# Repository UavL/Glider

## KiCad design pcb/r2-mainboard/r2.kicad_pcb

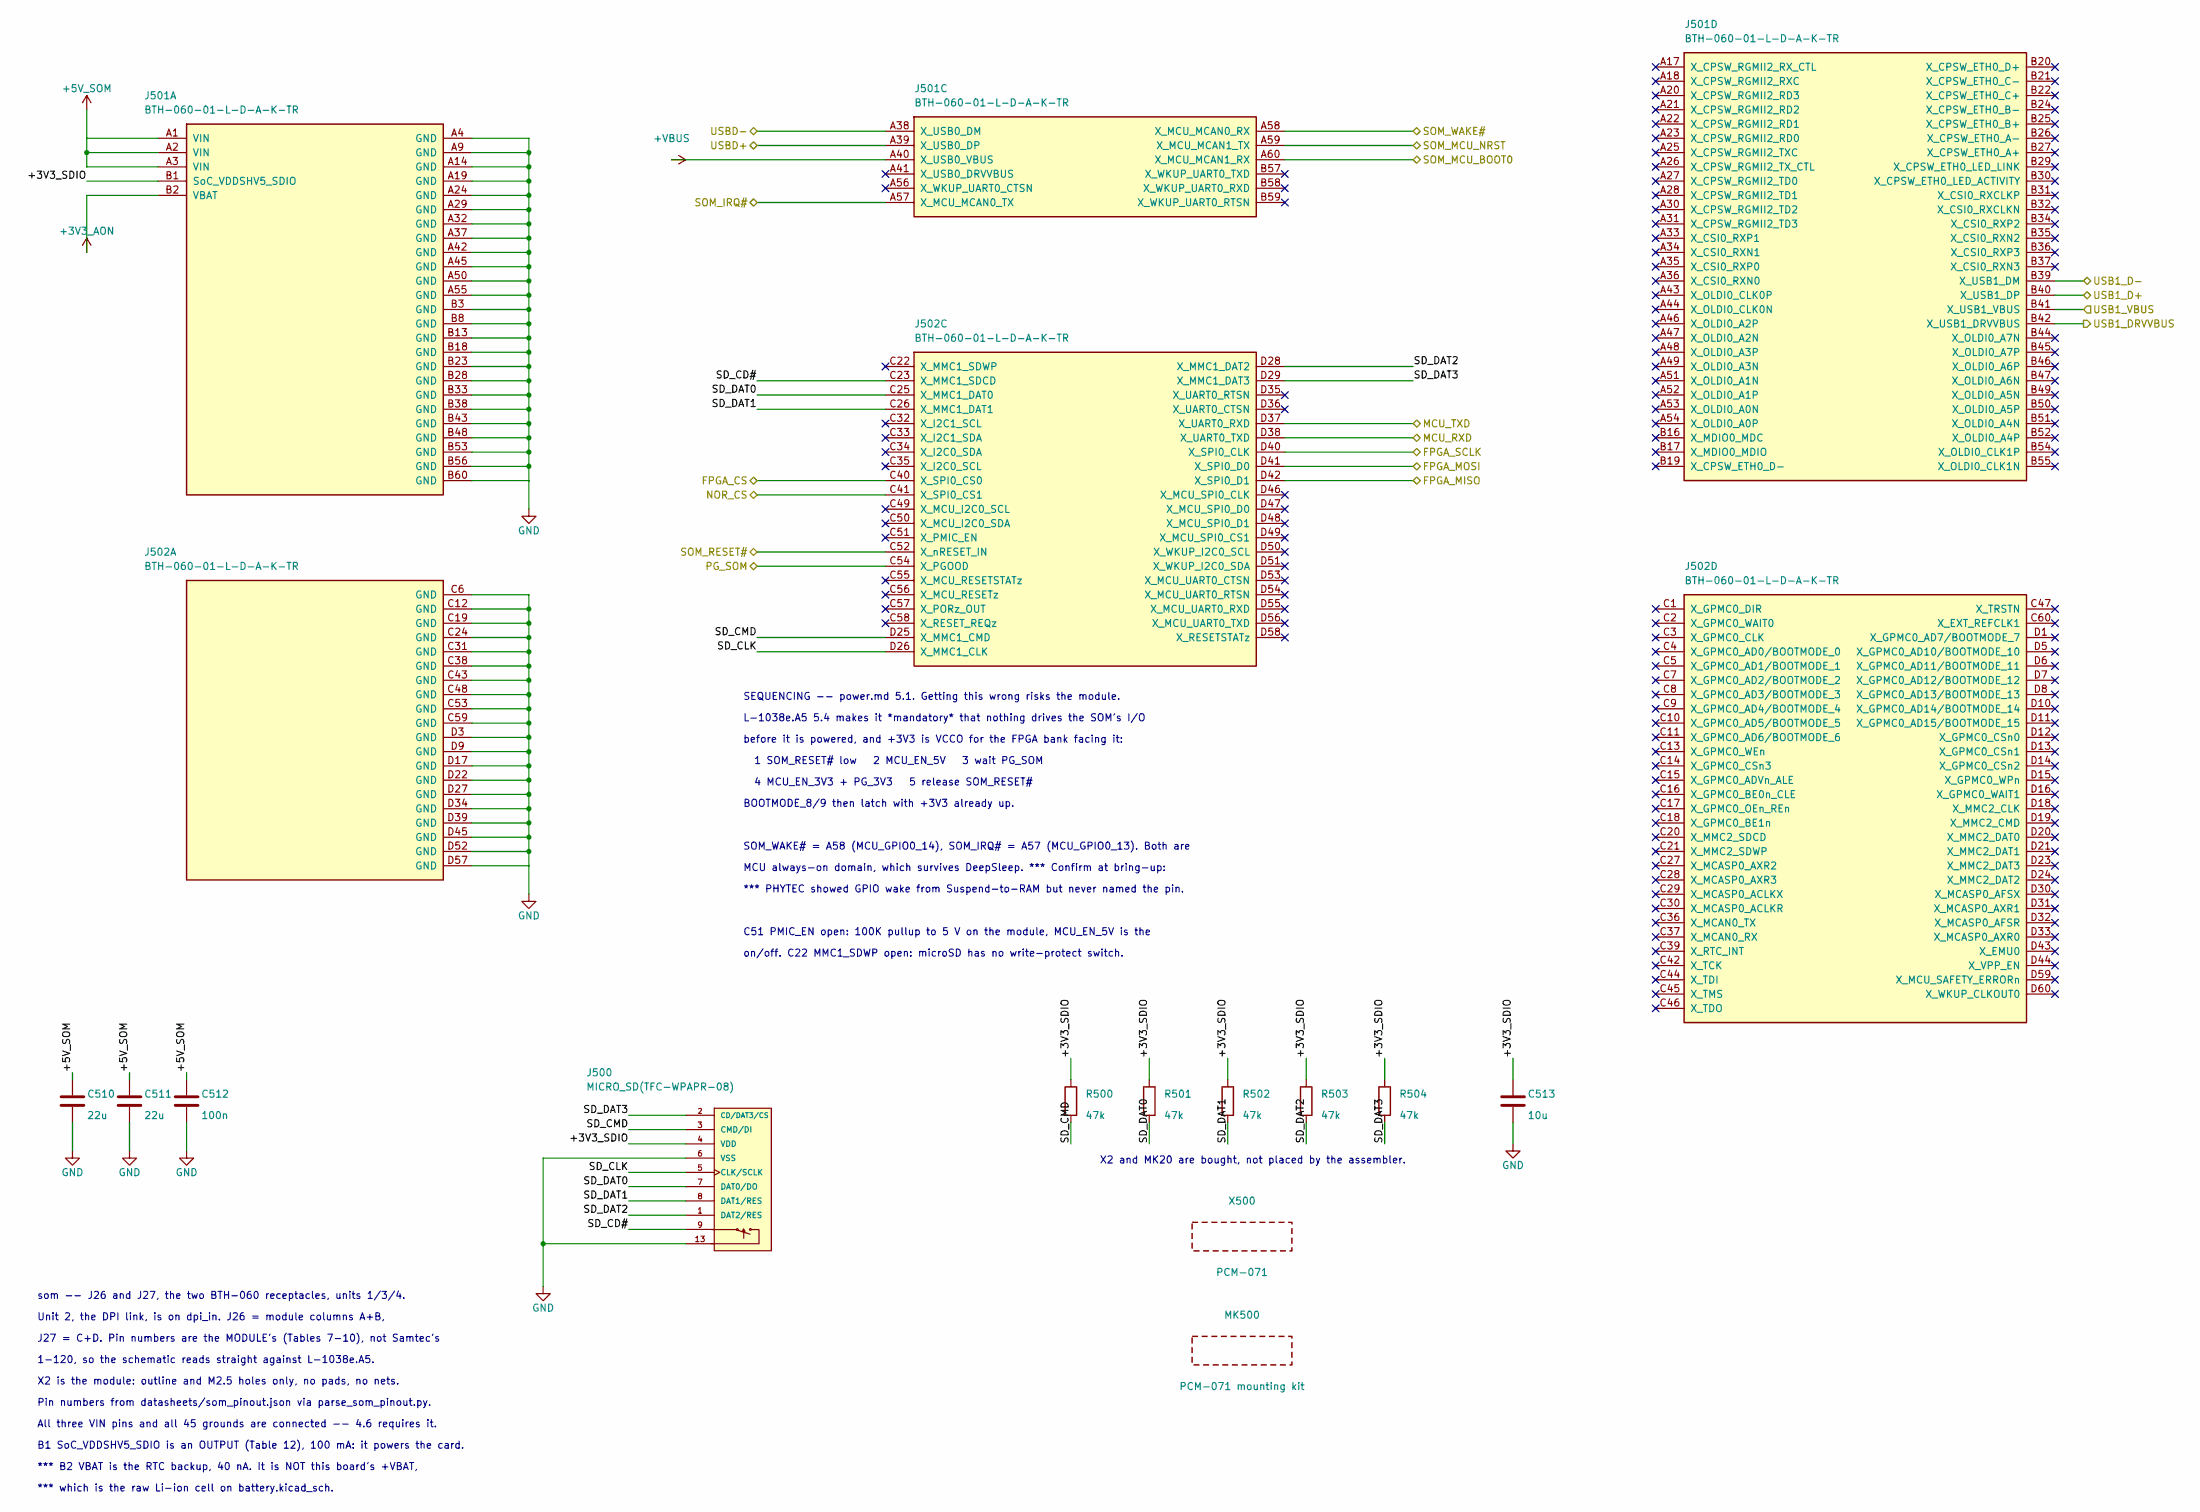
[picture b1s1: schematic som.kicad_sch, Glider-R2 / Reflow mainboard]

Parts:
C510, C511: 22u; C_0805_2012Metric
C512: 100n; C_0402_1005Metric
C513: 10u; C_0805_2012Metric
J500: MICRO_SD(TFC-WPAPR-08); TFC-WPAPR-08
J501: BTH-060-01-L-D-A-K-TR; BTH-060-01-L-D-A-K_AB; MPN BTH-060-01-L-D-A-K-TR; LCSC C3646540
J502: BTH-060-01-L-D-A-K-TR; BTH-060-01-L-D-A-K_CD; MPN BTH-060-01-L-D-A-K-TR; LCSC C3646540
MK500: PCM-071 mounting kit; MPN 2x M2.5x5 F-F standoff, 4x M2.5x4 screw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
R500, R501, R502, R503, R504: 47k; R_0402_1005Metric
X500: PCM-071; PCM-071_Module; MPN PCM-071

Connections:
+3V3_AON: J501.B2 (VBAT); also elsewhere on the board
+5V_SOM: C510.1, C511.1, C512.1, J501.A1 (VIN), J501.A2 (VIN), J501.A3 (VIN); also elsewhere on the board
+VBUS: J501.A40 (X_USB0_VBUS); also elsewhere on the board
/FPGA_CS: J502.C40 (X_SPI0_CS0); also elsewhere on the board
/FPGA_MISO: J502.D42 (X_SPI0_D1); also elsewhere on the board
/FPGA_MOSI: J502.D41 (X_SPI0_D0); also elsewhere on the board
/FPGA_SCLK: J502.D40 (X_SPI0_CLK); also elsewhere on the board
/MCU_RXD: J502.D38 (X_UART0_TXD); also elsewhere on the board
/MCU_TXD: J502.D37 (X_UART0_RXD); also elsewhere on the board
/NOR_CS: J502.C41 (X_SPI0_CS1); also elsewhere on the board
/PG_SOM: J502.C54 (X_PGOOD); also elsewhere on the board
/SOM_IRQ#: J501.A57 (X_MCU_MCAN0_TX); also elsewhere on the board
/SOM_MCU_BOOT0: J501.A60 (X_MCU_MCAN1_RX); also elsewhere on the board
/SOM_MCU_NRST: J501.A59 (X_MCU_MCAN1_TX); also elsewhere on the board
/SOM_RESET#: J502.C52 (X_nRESET_IN); also elsewhere on the board
/SOM_WAKE#: J501.A58 (X_MCU_MCAN0_RX); also elsewhere on the board
/USB1_D+: J501.B40 (X_USB1_DP); also elsewhere on the board
/USB1_D-: J501.B39 (X_USB1_DM); also elsewhere on the board
/USB1_DRVVBUS: J501.B42 (X_USB1_DRVVBUS); also elsewhere on the board
/USB1_VBUS: J501.B41 (X_USB1_VBUS); also elsewhere on the board
/USBD+: J501.A39 (X_USB0_DP); also elsewhere on the board
/USBD-: J501.A38 (X_USB0_DM); also elsewhere on the board
/som/+3V3_SDIO: C513.1, J500.4 (VDD), J501.B1 (SoC_VDDSHV5_SDIO), R500.1, R501.1, R502.1, R503.1, R504.1
/som/SD_CD#: J500.9, J502.C23 (X_MMC1_SDCD)
/som/SD_CLK: J500.5 (CLK/SCLK), J502.D26 (X_MMC1_CLK)
/som/SD_CMD: J500.3 (CMD/DI), J502.D25 (X_MMC1_CMD), R500.2
/som/SD_DAT0: J500.7 (DAT0/DO), J502.C25 (X_MMC1_DAT0), R501.2
/som/SD_DAT1: J500.8 (DAT1/RES), J502.C26 (X_MMC1_DAT1), R502.2
/som/SD_DAT2: J500.1 (DAT2/RES), J502.D28 (X_MMC1_DAT2), R503.2
/som/SD_DAT3: J500.2 (CD/DAT3/CS), J502.D29 (X_MMC1_DAT3), R504.2
GND: C510.2, C511.2, C512.2, C513.2, J500.6 (VSS), J500.10, J500.11, J500.12, J500.13, J501.A4 (GND), J501.A9 (GND), J501.A14 (GND), J501.A19 (GND), J501.A24 (GND), J501.A29 (GND), J501.A32 (GND), J501.A37 (GND), J501.A42 (GND), J501.A45 (GND), J501.A50 (GND), J501.A55 (GND), J501.B3 (GND), J501.B8 (GND), J501.B13 (GND), J501.B18 (GND), J501.B23 (GND), J501.B28 (GND), J501.B33 (GND), J501.B38 (GND), J501.B43 (GND), J501.B48 (GND), J501.B53 (GND), J501.B56 (GND), J501.B60 (GND), J502.C6 (GND), J502.C12 (GND), J502.C19 (GND), J502.C24 (GND), J502.C31 (GND), J502.C38 (GND), J502.C43 (GND), J502.C48 (GND), J502.C53 (GND), J502.C59 (GND), J502.D3 (GND), J502.D9 (GND), J502.D17 (GND), J502.D22 (GND), J502.D27 (GND), J502.D34 (GND), J502.D39 (GND), J502.D45 (GND), J502.D52 (GND), J502.D57 (GND); also elsewhere on the board

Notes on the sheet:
4 MCU_EN_3V3 + PG_3V3 5 release SOM_RESET#
*** B2 VBAT is the RTC backup, 40 nA. It is NOT this board's +VBAT,
MCU always-on domain, which survives DeepSleep. *** Confirm at bring-up:
BOOTMODE_8/9 then latch with +3V3 already up.
Unit 2, the DPI link, is on dpi_in. J26 = module columns A+B,
Pin numbers from datasheets/som_pinout.json via parse_som_pinout.py.
*** which is the raw Li-ion cell on battery.kicad_sch.
on/off. C22 MMC1_SDWP open: microSD has no write-protect switch.
before it is powered, and +3V3 is VCCO for the FPGA bank facing it:
SEQUENCING -- power.md 5.1. Getting this wrong risks the module.
X2 is the module: outline and M2.5 holes only, no pads, no nets.
B1 SoC_VDDSHV5_SDIO is an OUTPUT (Table 12), 100 mA: it powers the card.
J27 = C+D. Pin numbers are the MODULE's (Tables 7-10), not Samtec's
SOM_WAKE# = A58 (MCU_GPIO0_14), SOM_IRQ# = A57 (MCU_GPIO0_13). Both are
C51 PMIC_EN open: 100K pullup to 5 V on the module, MCU_EN_5V is the
som -- J26 and J27, the two BTH-060 receptacles, units 1/3/4.
1 SOM_RESET# low 2 MCU_EN_5V 3 wait PG_SOM
X2 and MK20 are bought, not placed by the assembler.
*** PHYTEC showed GPIO wake from Suspend-to-RAM but never named the pin.
All three VIN pins and all 45 grounds are connected -- 4.6 requires it.
1-120, so the schematic reads straight against L-1038e.A5.
L-1038e.A5 5.4 makes it *mandatory* that nothing drives the SOM's I/O

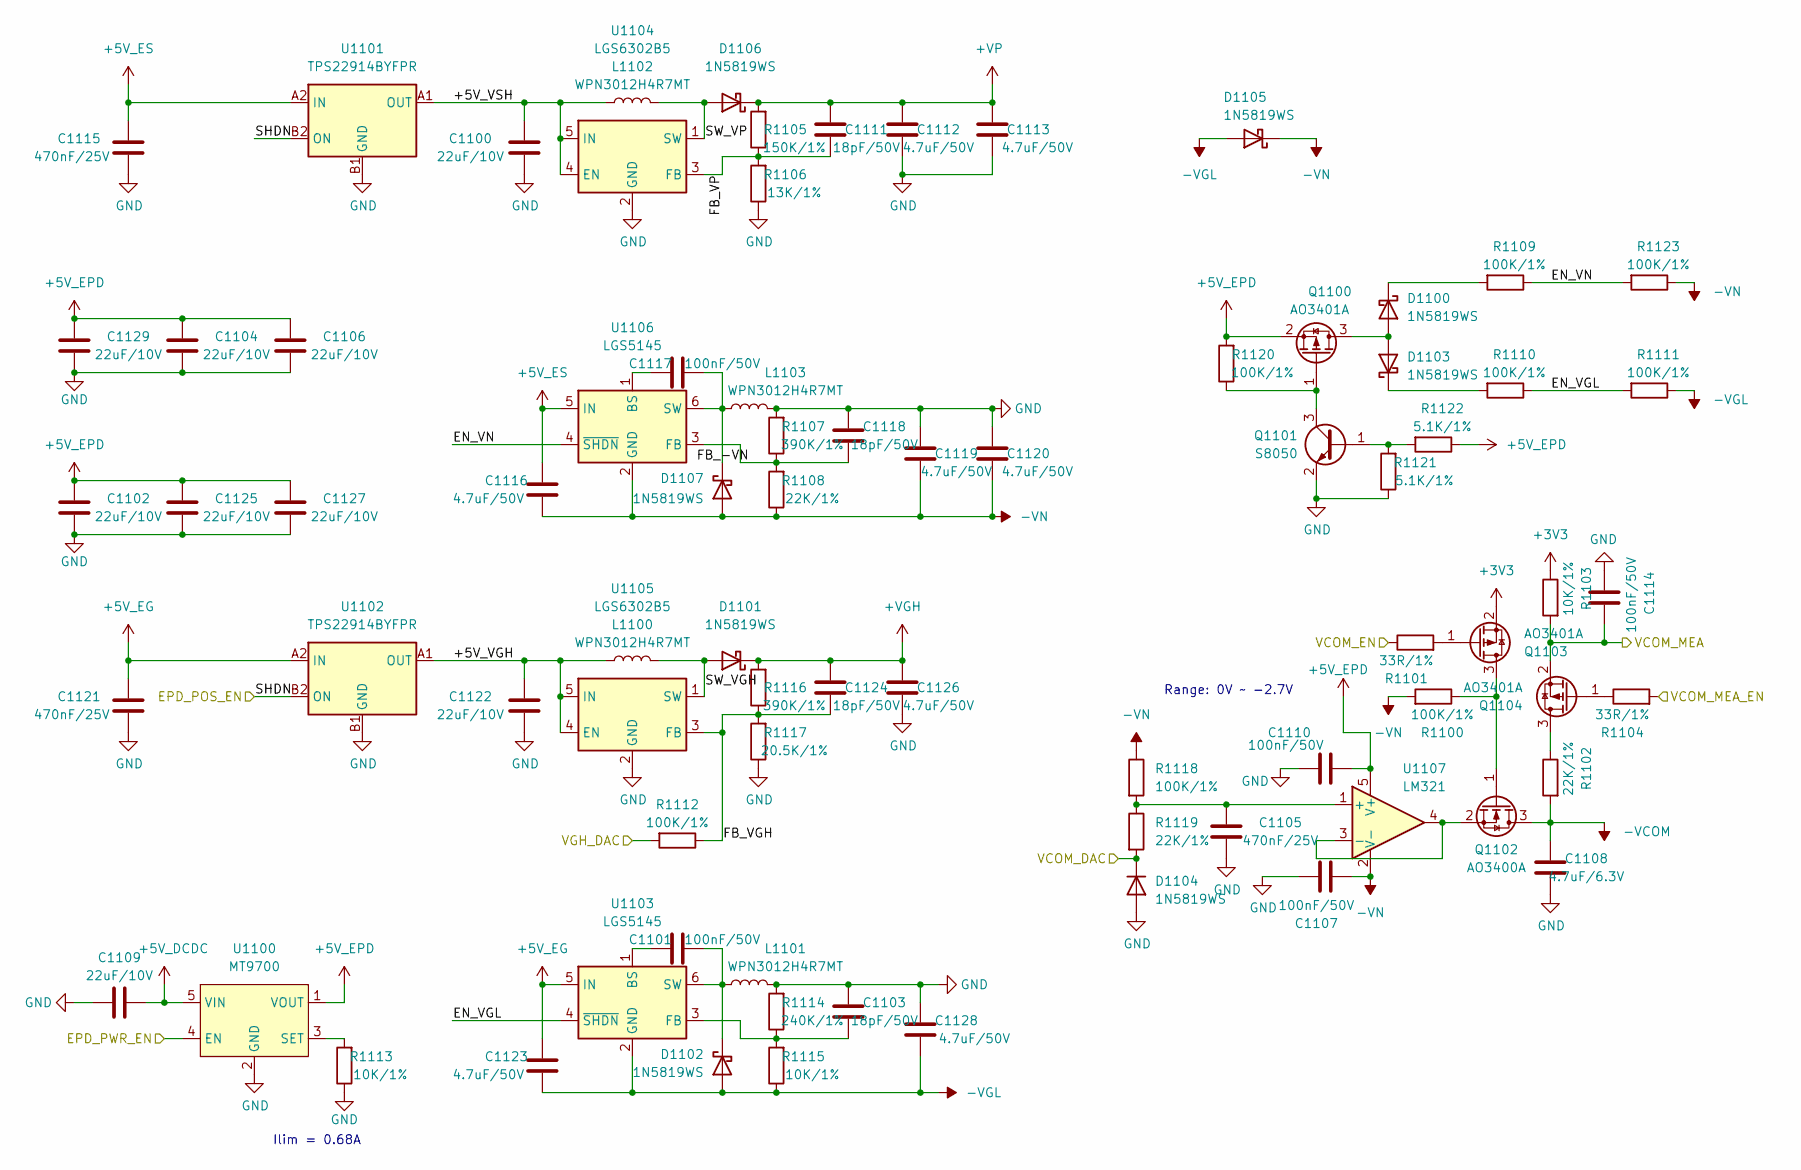
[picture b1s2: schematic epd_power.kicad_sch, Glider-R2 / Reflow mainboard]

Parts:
C1100, C1102, C1104, C1106, C1109, C1122, C1125, C1127, C1129: 22uF/10V; C_0805_2012Metric; MPN CL21A226MPQNNNE; LCSC C29277
C1101, C1107, C1110, C1114, C1117: 100nF/50V; C_0402_1005Metric; MPN CC0402KRX7R9BB104; LCSC C131394
C1103, C1111, C1118, C1124: 18pF/50V; C_0402_1005Metric; MPN CC0402JRNPO9BN180; LCSC C106202
C1105, C1115, C1121: 470nF/25V; C_0402_1005Metric; MPN CGA0402X5R474K250GT; LCSC C6119801
C1108: 4.7uF/6.3V; C_0402_1005Metric; MPN CL05A475MQ5NRNC; LCSC C307423
C1112, C1113, C1116, C1119, C1120, C1123, C1126, C1128: 4.7uF/50V; C_0805_2012Metric; MPN CGA0805X5R475K500MT; LCSC C6119903
D1100, D1101, D1102, D1103, D1105, D1106, D1107: 1N5819WS; D_SOD-323; MPN B5819WS; LCSC C488405
D1104: 1N5819WS; D_SOD-323_Alt; MPN B5819WS; LCSC C488405
L1100, L1101, L1102, L1103: WPN3012H4R7MT; L_Changjiang_FNR3012S; MPN WPN3012H4R7MT; LCSC C98357
Q1100, Q1103, Q1104: AO3401A; SOT-23; MPN AO3401A; LCSC C347476
Q1101: S8050; SOT-23; MPN S8050; LCSC C444723
Q1102: AO3400A; SOT-23; MPN AO3400A; LCSC C347475
R1100, R1109, R1110, R1111, R1112, R1118, R1120, R1123: 100K/1%; R_0402_1005Metric; MPN 0402WGF1003TCE; LCSC C25741
R1101, R1104: 33R/1%; R_0402_1005Metric; MPN 0402WGF330JTCE; LCSC C25105
R1102, R1108, R1119: 22K/1%; R_0402_1005Metric; MPN 0402WGF2202TCE; LCSC C25768
R1103, R1113, R1115: 10K/1%; R_0402_1005Metric; MPN 0402WGF1002TCE; LCSC C25744
R1105: 150K/1%; R_0402_1005Metric; MPN 0402WGF1503TCE; LCSC C25755
R1106: 13K/1%; R_0402_1005Metric; MPN 0402WGF1302TCE; LCSC C25754
R1107, R1116: 390K/1%; R_0402_1005Metric; MPN HRC0402F3903DNTO; LCSC C54920667
R1114: 240K/1%; R_0402_1005Metric; MPN 0402WGF2403TCE; LCSC C64043
R1117: 20.5K/1%; R_0402_1005Metric; MPN 0402WGF2052TCE; LCSC C57105
R1121, R1122: 5.1K/1%; R_0402_1005Metric; MPN 0402WGF5101TCE; LCSC C25905
U1100: MT9700; SOT-23-5; MPN MT9700; LCSC C89855
U1101, U1102: TPS22914BYFPR; WLCSP-4_0.89x0.89mm_Layout2x2_P0.5mm; MPN TPS22914BYFPR; LCSC C1848394
U1103, U1106: LGS5145; TSOT-23-6; MPN LGS5145; LCSC C5123971
U1104, U1105: LGS6302B5; SOT-23-5; MPN LGS6302B5; LCSC C5123975
U1107: LM321; SOT-23-5; MPN LM321MFX/NOPB; LCSC C9405

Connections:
+3V3: Q1103.2 (S), R1103.1; also elsewhere on the board
+5V_DCDC: C1109.2, U1100.5 (VIN); also elsewhere on the board
+5V_EG: C1121.1, C1123.2, U1102.A2 (IN), U1103.5 (IN); also elsewhere on the board
+5V_EPD: C1102.2, C1104.2, C1106.2, C1110.2, C1125.2, C1127.2, C1129.2, Q1100.2 (S), R1120.2, R1122.1, U1100.1 (VOUT), U1107.5 (V+); also elsewhere on the board
+5V_ES: C1115.1, C1116.2, U1101.A2 (IN), U1106.5 (IN); also elsewhere on the board
+VGH: C1124.2, C1126.2, D1101.1 (K), R1116.2; also elsewhere on the board
+VP: C1111.2, C1112.2, C1113.2, D1106.1 (K), R1105.2; also elsewhere on the board
-VCOM: C1108.2, Q1102.3 (D), R1102.2; also elsewhere on the board
-VGL: C1123.1, C1128.1, D1102.2 (A), D1105.2 (A), R1111.1, R1115.1, U1103.2 (GND); also elsewhere on the board
-VN: C1107.2, C1116.1, C1119.1, C1120.1, D1105.1 (K), D1107.2 (A), R1100.2, R1108.1, R1118.1, R1123.1, U1106.2 (GND), U1107.2 (V-); also elsewhere on the board
/EPD_POS_EN: U1101.B2 (ON), U1102.B2 (ON); also elsewhere on the board
/EPD_PWR_EN: U1100.4 (EN); also elsewhere on the board
/VCOM_DAC: D1104.1 (K), R1119.2; also elsewhere on the board
/VCOM_EN: R1101.1; also elsewhere on the board
/VCOM_MEA: C1114.2, Q1104.2 (S), R1103.2; also elsewhere on the board
/VCOM_MEA_EN: R1104.2; also elsewhere on the board
/VGH_DAC: R1112.2; also elsewhere on the board
/epd_power/+5V_VGH: C1122.2, L1100.1, U1102.A1 (OUT), U1105.4 (EN), U1105.5 (IN)
/epd_power/+5V_VSH: C1100.2, L1102.1, U1101.A1 (OUT), U1104.4 (EN), U1104.5 (IN)
/epd_power/EN_VGL: R1110.1, R1111.2, U1103.4 (~SHDN)
/epd_power/EN_VN: R1109.1, R1123.2, U1106.4 (~SHDN)
/epd_power/FB_-VN: C1118.1, R1107.1, R1108.2, U1106.3 (FB)
/epd_power/FB_VGH: C1124.1, R1112.1, R1116.1, R1117.2, U1105.3 (FB)
/epd_power/FB_VP: C1111.1, R1105.1, R1106.2, U1104.3 (FB)
/epd_power/SW_VGH: D1101.2 (A), L1100.2, U1105.1 (SW)
/epd_power/SW_VP: D1106.2 (A), L1102.2, U1104.1 (SW)
GND: C1100.1, C1102.1, C1103.2, C1104.1, C1105.1, C1106.1, C1107.1, C1108.1, C1109.1, C1110.1, C1112.1, C1113.1, C1114.1, C1115.2, C1118.2, C1119.2, C1120.2, C1121.2, C1122.1, C1125.1, C1126.1, C1127.1, C1128.2, C1129.1, D1104.2 (A), L1101.2, L1103.2, Q1101.2 (E), R1106.1, R1107.2, R1113.1, R1114.2, R1117.1, R1121.1, U1100.2 (GND), U1101.B1 (GND), U1102.B1 (GND), U1104.2 (GND), U1105.2 (GND); also elsewhere on the board
unnamed: D1100.2 (A), D1103.2 (A), Q1100.3 (D)
unnamed: D1100.1 (K), R1109.2
unnamed: C1101.1, D1102.1 (K), L1101.1, U1103.6 (SW)
unnamed: D1103.1 (K), R1110.2
unnamed: C1117.1, D1107.1 (K), L1103.1, U1106.6 (SW)
unnamed: Q1100.1 (G), Q1101.3 (C), R1120.1
unnamed: Q1101.1 (B), R1121.2, R1122.2
unnamed: Q1102.1 (G), Q1103.3 (D), R1100.1
unnamed: Q1102.2 (S), U1107.3 (-), U1107.4
unnamed: Q1103.1 (G), R1101.2
unnamed: Q1104.3 (D), R1102.1
unnamed: Q1104.1 (G), R1104.1
unnamed: R1113.2, U1100.3 (SET)
unnamed: C1101.2, U1103.1 (BS)
unnamed: C1103.1, R1114.1, R1115.2, U1103.3 (FB)
unnamed: C1117.2, U1106.1 (BS)
unnamed: C1105.2, R1118.2, R1119.1, U1107.1 (+)

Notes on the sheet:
Ilim = 0.68A
Range: 0V ~ -2.7V

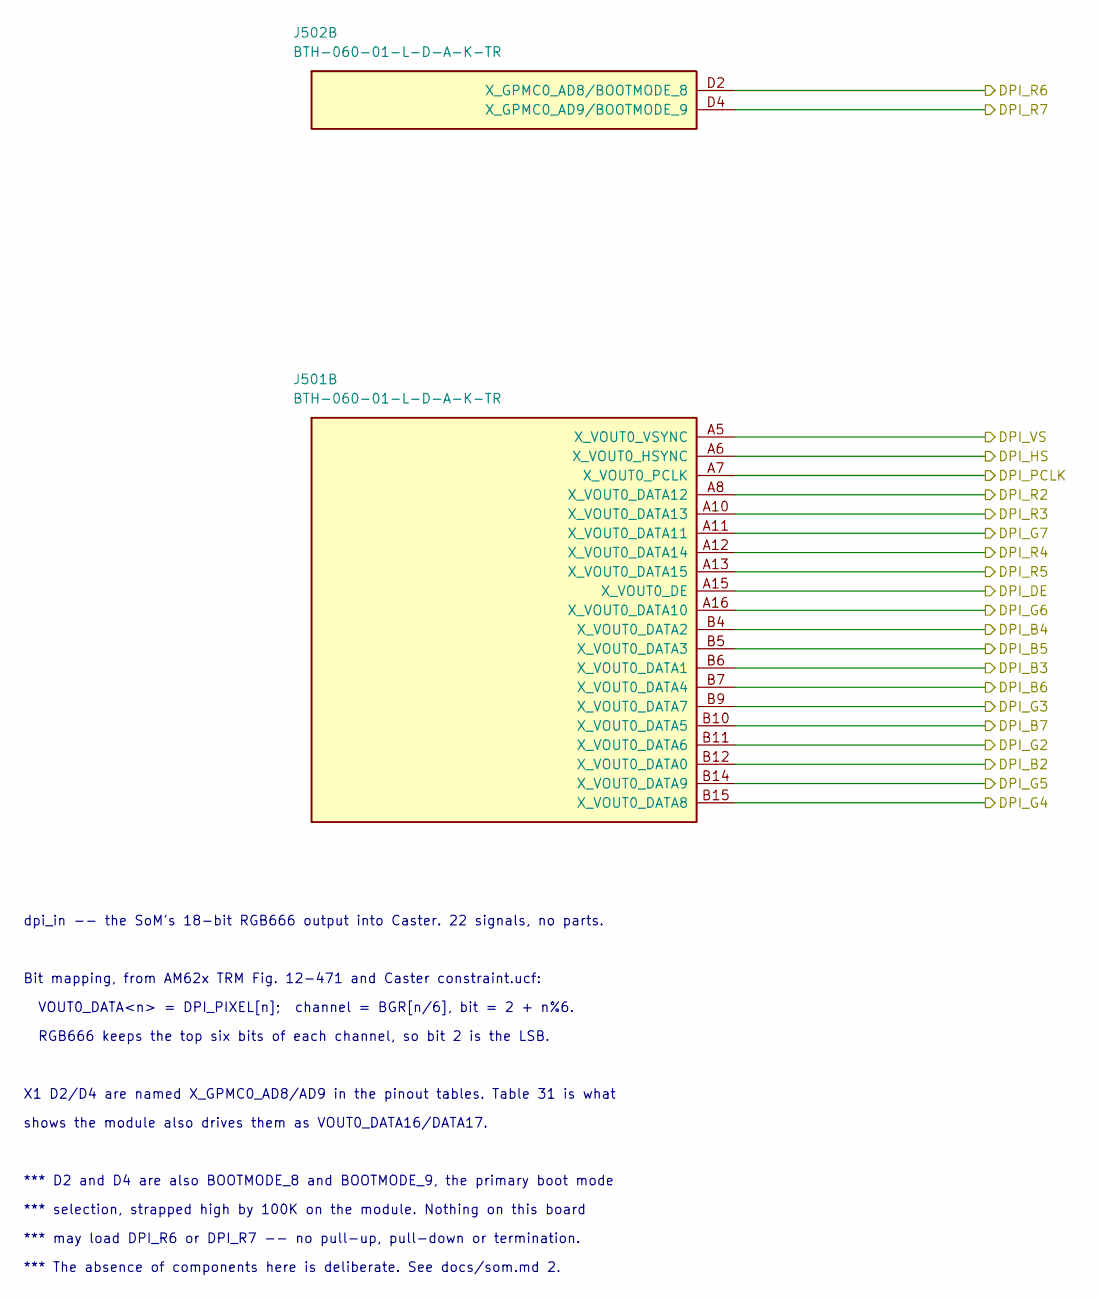
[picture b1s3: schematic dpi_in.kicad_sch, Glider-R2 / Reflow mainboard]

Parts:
J501: BTH-060-01-L-D-A-K-TR; BTH-060-01-L-D-A-K_AB; MPN BTH-060-01-L-D-A-K-TR; LCSC C3646540
J502: BTH-060-01-L-D-A-K-TR; BTH-060-01-L-D-A-K_CD; MPN BTH-060-01-L-D-A-K-TR; LCSC C3646540

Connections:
/DPI_B2: J501.B12 (X_VOUT0_DATA0); also elsewhere on the board
/DPI_B3: J501.B6 (X_VOUT0_DATA1); also elsewhere on the board
/DPI_B4: J501.B4 (X_VOUT0_DATA2); also elsewhere on the board
/DPI_B5: J501.B5 (X_VOUT0_DATA3); also elsewhere on the board
/DPI_B6: J501.B7 (X_VOUT0_DATA4); also elsewhere on the board
/DPI_B7: J501.B10 (X_VOUT0_DATA5); also elsewhere on the board
/DPI_DE: J501.A15 (X_VOUT0_DE); also elsewhere on the board
/DPI_G2: J501.B11 (X_VOUT0_DATA6); also elsewhere on the board
/DPI_G3: J501.B9 (X_VOUT0_DATA7); also elsewhere on the board
/DPI_G4: J501.B15 (X_VOUT0_DATA8); also elsewhere on the board
/DPI_G5: J501.B14 (X_VOUT0_DATA9); also elsewhere on the board
/DPI_G6: J501.A16 (X_VOUT0_DATA10); also elsewhere on the board
/DPI_G7: J501.A11 (X_VOUT0_DATA11); also elsewhere on the board
/DPI_HS: J501.A6 (X_VOUT0_HSYNC); also elsewhere on the board
/DPI_PCLK: J501.A7 (X_VOUT0_PCLK); also elsewhere on the board
/DPI_R2: J501.A8 (X_VOUT0_DATA12); also elsewhere on the board
/DPI_R3: J501.A10 (X_VOUT0_DATA13); also elsewhere on the board
/DPI_R4: J501.A12 (X_VOUT0_DATA14); also elsewhere on the board
/DPI_R5: J501.A13 (X_VOUT0_DATA15); also elsewhere on the board
/DPI_R6: J502.D2 (X_GPMC0_AD8/BOOTMODE_8); also elsewhere on the board
/DPI_R7: J502.D4 (X_GPMC0_AD9/BOOTMODE_9); also elsewhere on the board
/DPI_VS: J501.A5 (X_VOUT0_VSYNC); also elsewhere on the board

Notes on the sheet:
dpi_in -- the SoM's 18-bit RGB666 output into Caster. 22 signals, no parts.
*** The absence of components here is deliberate. See docs/som.md 2.
RGB666 keeps the top six bits of each channel, so bit 2 is the LSB.
*** may load DPI_R6 or DPI_R7 -- no pull-up, pull-down or termination.
shows the module also drives them as VOUT0_DATA16/DATA17.
VOUT0_DATA<n> = DPI_PIXEL[n]; channel = BGR[n/6], bit = 2 + n%6.
X1 D2/D4 are named X_GPMC0_AD8/AD9 in the pinout tables. Table 31 is what
Bit mapping, from AM62x TRM Fig. 12-471 and Caster constraint.ucf:
*** selection, strapped high by 100K on the module. Nothing on this board
*** D2 and D4 are also BOOTMODE_8 and BOOTMODE_9, the primary boot mode

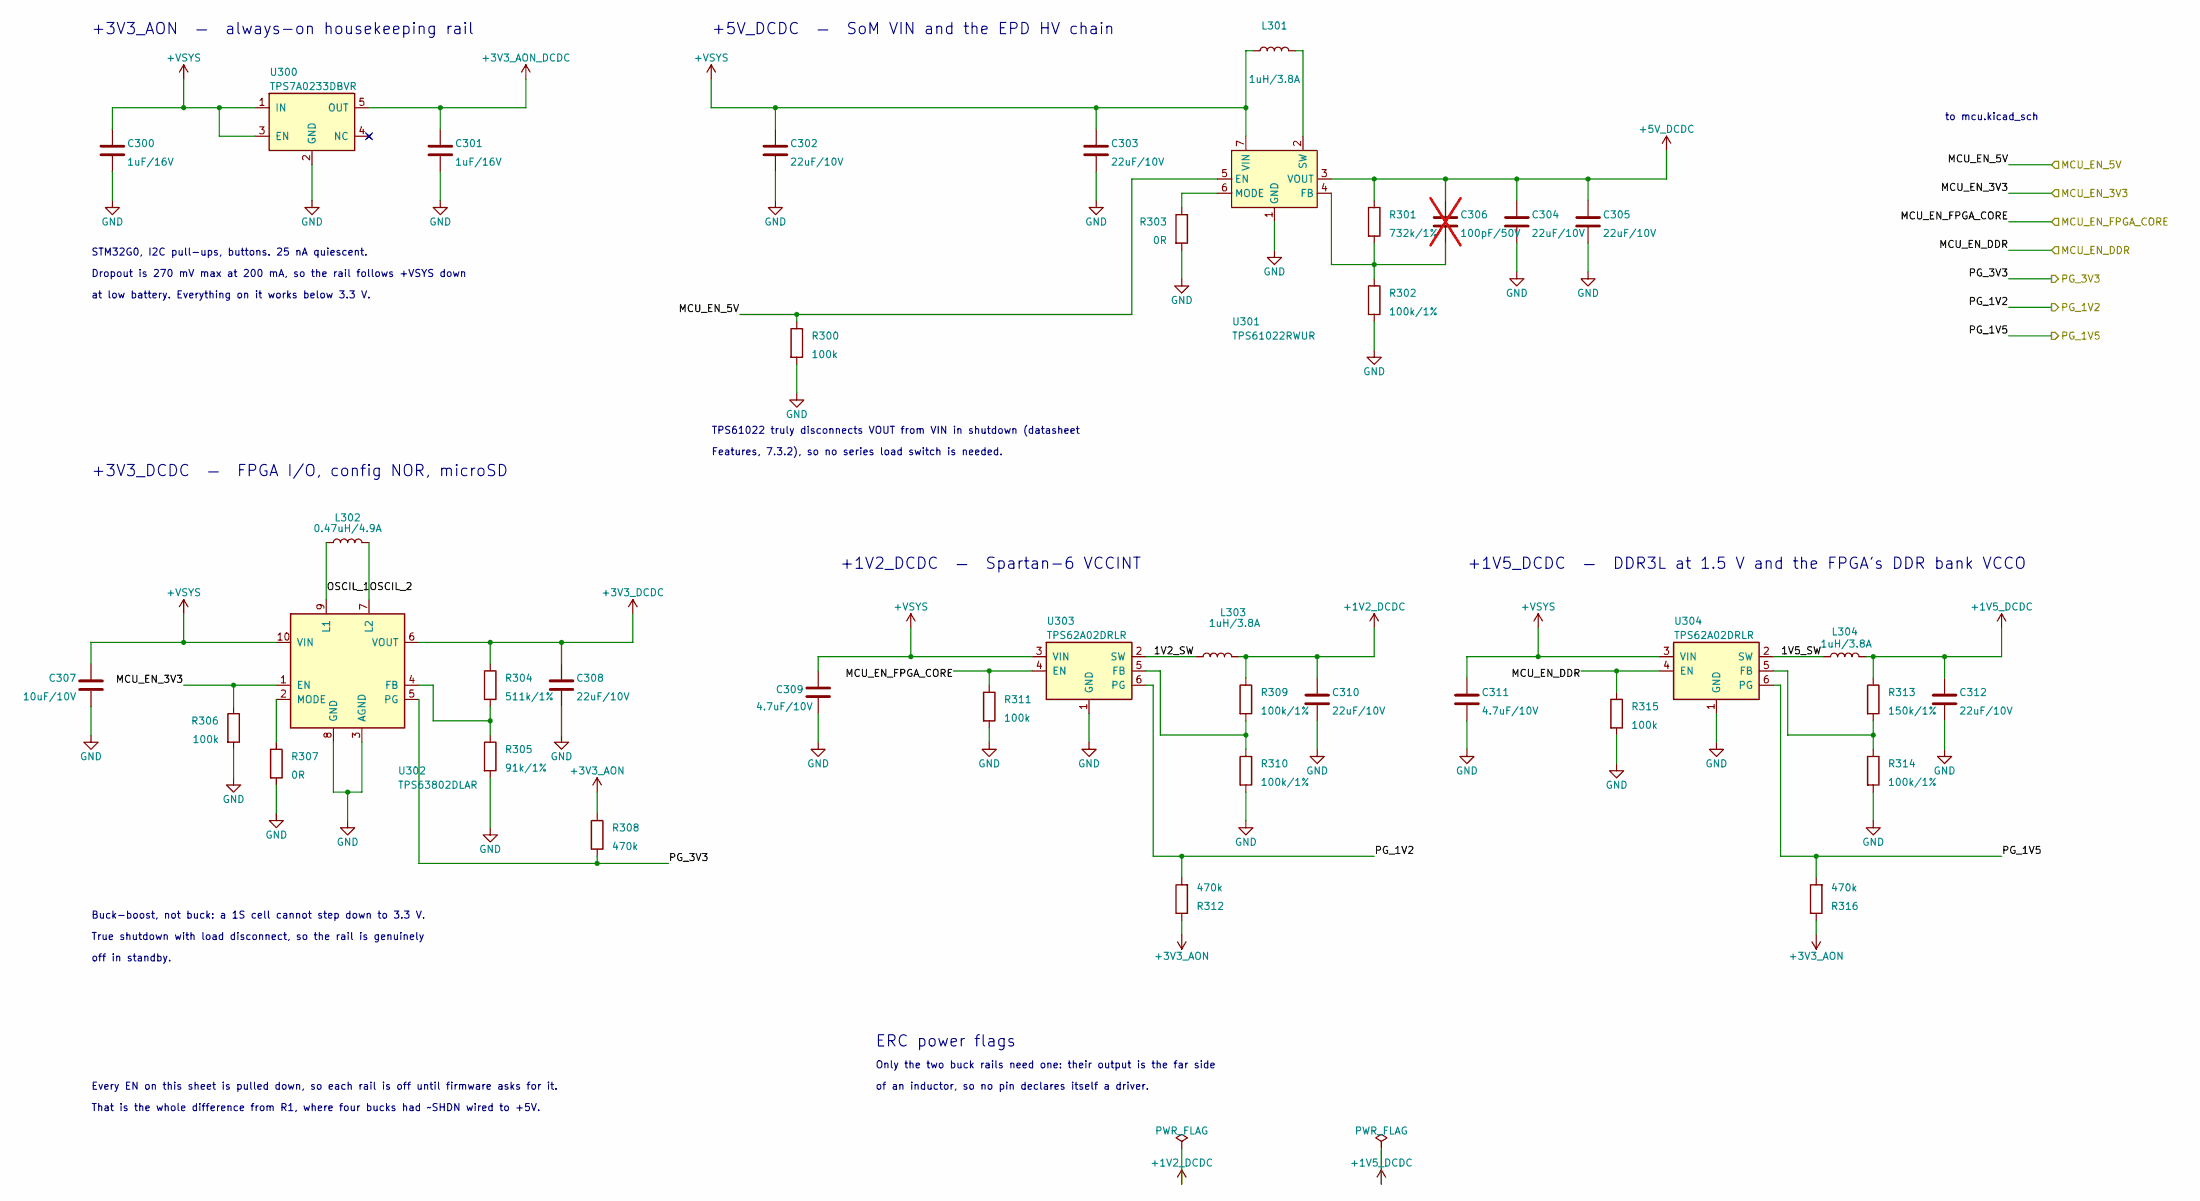
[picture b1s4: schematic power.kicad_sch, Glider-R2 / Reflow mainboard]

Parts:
C300, C301: 1uF/16V; C_0402_1005Metric
C302, C303, C304, C305, C308, C310, C312: 22uF/10V; C_0805_2012Metric; MPN CL21A226MPQNNNE
C306: 100pF/50V; C_0402_1005Metric; not fitted
C307: 10uF/10V; C_0805_2012Metric
C309, C311: 4.7uF/10V; C_0805_2012Metric
L301, L303, L304: 1uH/3.8A; L_1210_3225Metric; MPN DFE322512F-1R0M; LCSC C3224227
L302: 0.47uH/4.9A; L_1008_2520Metric; MPN DFE252012F-R47M; LCSC C703140
R300, R306, R311, R315: 100k; R_0402_1005Metric
R301: 732k/1%; R_0402_1005Metric
R302, R309, R310, R314: 100k/1%; R_0402_1005Metric
R303, R307: 0R; R_0402_1005Metric
R304: 511k/1%; R_0402_1005Metric
R305: 91k/1%; R_0402_1005Metric
R308, R312, R316: 470k; R_0402_1005Metric
R313: 150k/1%; R_0402_1005Metric
U300: TPS7A0233DBVR; SOT-23-5; MPN TPS7A0233DBVR; LCSC C5142805
U301: TPS61022RWUR; Texas_RWU0007A_VQFN-7_2x2mm_P0.5mm; MPN TPS61022RWUR; LCSC C915088
U302: TPS63802DLAR; Texas_DLA0010A_VSON-HR-10_2x3mm_P0.5mm; MPN TPS63802DLAR; LCSC C2845237
U303, U304: TPS62A02DRLR; SOT-563; MPN TPS62A02DRLR; LCSC C5350187

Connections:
+1V2_DCDC: C310.1, L303.2, R309.1; also elsewhere on the board
+1V5_DCDC: C312.1, L304.2, R313.1; also elsewhere on the board
+3V3_AON: R308.1, R312.1, R316.1; also elsewhere on the board
+3V3_AON_DCDC: C301.1, U300.5 (OUT); also elsewhere on the board
+3V3_DCDC: C308.1, R304.1, U302.6 (VOUT); also elsewhere on the board
+5V_DCDC: C304.1, C305.1, C306.1, R301.1, U301.3 (VOUT); also elsewhere on the board
+VSYS: C300.1, C302.1, C303.1, C307.1, C309.1, C311.1, L301.1, U300.1 (IN), U300.3 (EN), U301.7 (VIN), U302.10 (VIN), U303.3 (VIN), U304.3 (VIN); also elsewhere on the board
/MCU_EN_3V3: R306.1, U302.1 (EN); also elsewhere on the board
/MCU_EN_5V: R300.1, U301.5 (EN); also elsewhere on the board
/MCU_EN_DDR: R315.1, U304.4 (EN); also elsewhere on the board
/MCU_EN_FPGA_CORE: R311.1, U303.4 (EN); also elsewhere on the board
/PG_1V2: R312.2, U303.6 (PG); also elsewhere on the board
/PG_1V5: R316.2, U304.6 (PG); also elsewhere on the board
/PG_3V3: R308.2, U302.5 (PG); also elsewhere on the board
/power/1V2_SW: L303.1, U303.2 (SW)
/power/1V5_SW: L304.1, U304.2 (SW)
/power/OSCIL_1: L302.1, U302.9 (L1)
/power/OSCIL_2: L302.2, U302.7 (L2)
GND: C300.2, C301.2, C302.2, C303.2, C304.2, C305.2, C307.2, C308.2, C309.2, C310.2, C311.2, C312.2, R300.2, R302.2, R303.2, R305.2, R306.2, R307.2, R310.2, R311.2, R314.2, R315.2, U300.2 (GND), U301.1 (GND), U302.3 (AGND), U302.8 (GND), U303.1 (GND), U304.1 (GND); also elsewhere on the board
unnamed: C306.2, R301.2, R302.1, U301.4 (FB)
unnamed: R303.1, U301.6 (MODE)
unnamed: L301.2, U301.2 (SW)
unnamed: R304.2, R305.1, U302.4 (FB)
unnamed: R307.1, U302.2 (MODE)
unnamed: R309.2, R310.1, U303.5 (FB)
unnamed: R313.2, R314.1, U304.5 (FB)

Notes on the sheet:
+5V_DCDC — SoM VIN and the EPD HV chain
off in standby.
at low battery. Everything on it works below 3.3 V.
to mcu.kicad_sch
True shutdown with load disconnect, so the rail is genuinely
Dropout is 270 mV max at 200 mA, so the rail follows +VSYS down
TPS61022 truly disconnects VOUT from VIN in shutdown (datasheet
+3V3_AON — always-on housekeeping rail
STM32G0, I2C pull-ups, buttons. 25 nA quiescent.
Every EN on this sheet is pulled down, so each rail is off until firmware asks for it.
Features, 7.3.2), so no series load switch is needed.
+1V5_DCDC — DDR3L at 1.5 V and the FPGA's DDR bank VCCO
ERC power flags
Buck-boost, not buck: a 1S cell cannot step down to 3.3 V.
+1V2_DCDC — Spartan-6 VCCINT
Only the two buck rails need one: their output is the far side
That is the whole difference from R1, where four bucks had ~SHDN wired to +5V.
of an inductor, so no pin declares itself a driver.
+3V3_DCDC — FPGA I/O, config NOR, microSD

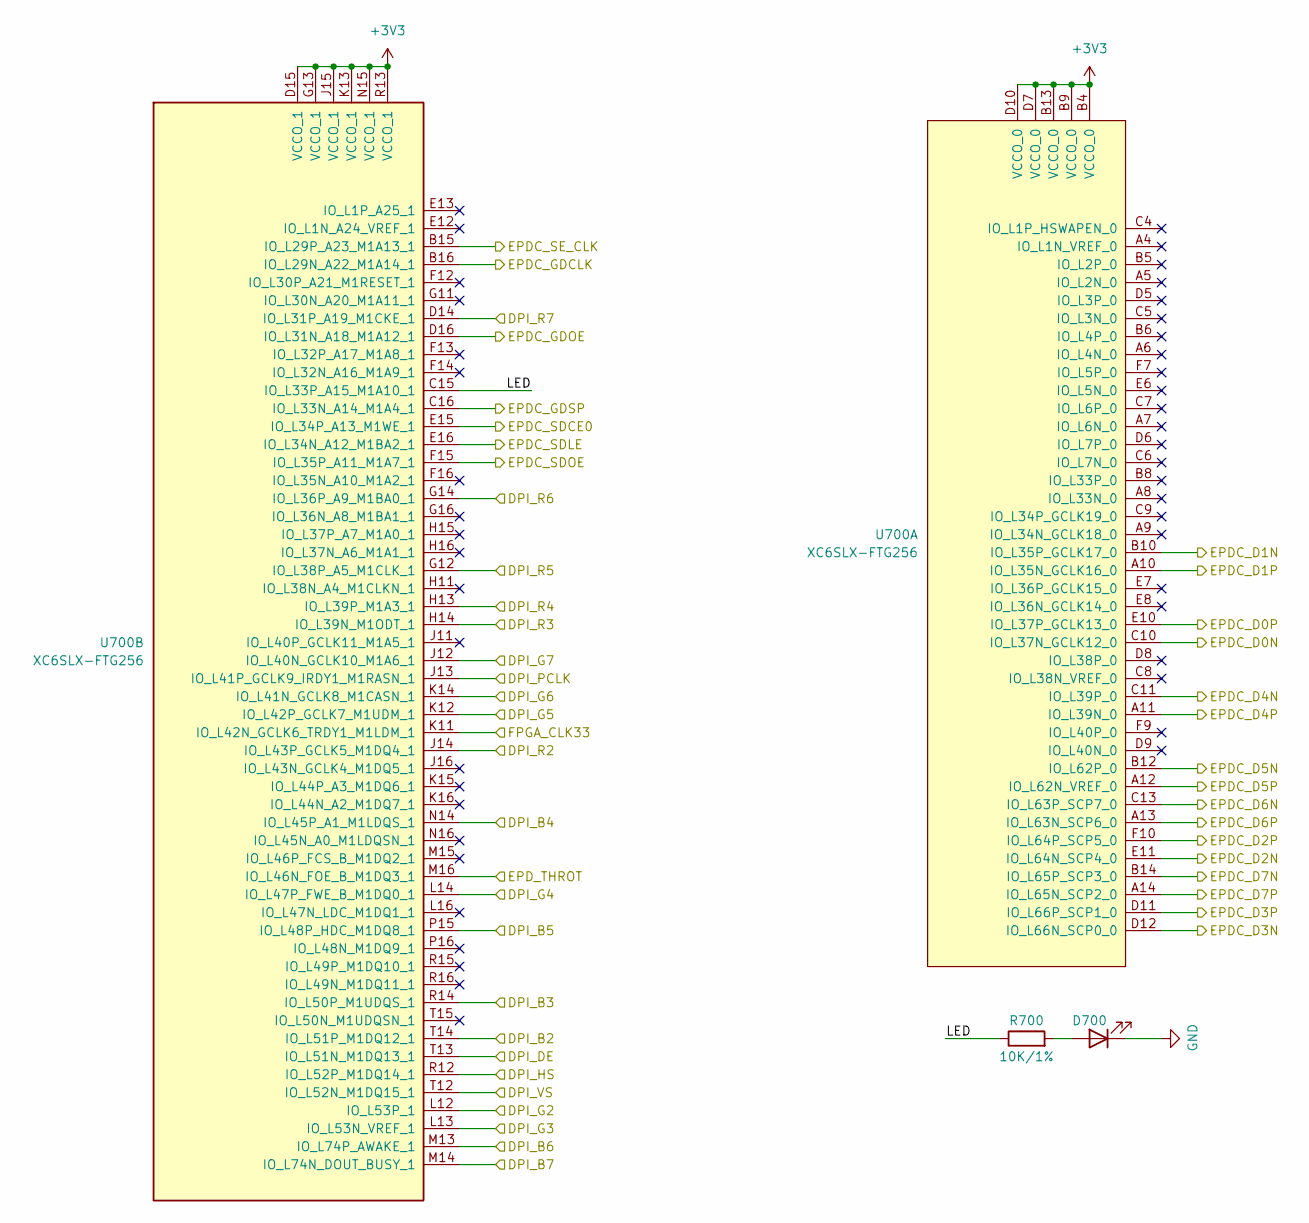
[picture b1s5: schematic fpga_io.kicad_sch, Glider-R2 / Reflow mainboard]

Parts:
D700: LED GREEN; LED_0603_1608Metric; MPN XL-1608UGC-04; LCSC C965804
R700: 10K/1%; R_0402_1005Metric; MPN 0402WGF1002TCE; LCSC C25744
U700: XC6SLX-FTG256; Xilinx_FTG256; MPN XC6SLX16-2FTG256C; LCSC C39313

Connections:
+3V3: U700.B4 (VCCO_0), U700.B9 (VCCO_0), U700.B13 (VCCO_0), U700.D7 (VCCO_0), U700.D10 (VCCO_0), U700.D15 (VCCO_1), U700.G13 (VCCO_1), U700.J15 (VCCO_1), U700.K13 (VCCO_1), U700.N15 (VCCO_1), U700.R13 (VCCO_1); also elsewhere on the board
/DPI_B2: U700.T14 (IO_L51P_M1DQ12_1); also elsewhere on the board
/DPI_B3: U700.R14 (IO_L50P_M1UDQS_1); also elsewhere on the board
/DPI_B4: U700.N14 (IO_L45P_A1_M1LDQS_1); also elsewhere on the board
/DPI_B5: U700.P15 (IO_L48P_HDC_M1DQ8_1); also elsewhere on the board
/DPI_B6: U700.M13 (IO_L74P_AWAKE_1); also elsewhere on the board
/DPI_B7: U700.M14 (IO_L74N_DOUT_BUSY_1); also elsewhere on the board
/DPI_DE: U700.T13 (IO_L51N_M1DQ13_1); also elsewhere on the board
/DPI_G2: U700.L12 (IO_L53P_1); also elsewhere on the board
/DPI_G3: U700.L13 (IO_L53N_VREF_1); also elsewhere on the board
/DPI_G4: U700.L14 (IO_L47P_FWE_B_M1DQ0_1); also elsewhere on the board
/DPI_G5: U700.K12 (IO_L42P_GCLK7_M1UDM_1); also elsewhere on the board
/DPI_G6: U700.K14 (IO_L41N_GCLK8_M1CASN_1); also elsewhere on the board
/DPI_G7: U700.J12 (IO_L40N_GCLK10_M1A6_1); also elsewhere on the board
/DPI_HS: U700.R12 (IO_L52P_M1DQ14_1); also elsewhere on the board
/DPI_PCLK: U700.J13 (IO_L41P_GCLK9_IRDY1_M1RASN_1); also elsewhere on the board
/DPI_R2: U700.J14 (IO_L43P_GCLK5_M1DQ4_1); also elsewhere on the board
/DPI_R3: U700.H14 (IO_L39N_M1ODT_1); also elsewhere on the board
/DPI_R4: U700.H13 (IO_L39P_M1A3_1); also elsewhere on the board
/DPI_R5: U700.G12 (IO_L38P_A5_M1CLK_1); also elsewhere on the board
/DPI_R6: U700.G14 (IO_L36P_A9_M1BA0_1); also elsewhere on the board
/DPI_R7: U700.D14 (IO_L31P_A19_M1CKE_1); also elsewhere on the board
/DPI_VS: U700.T12 (IO_L52N_M1DQ15_1); also elsewhere on the board
/EPDC_D0N: U700.C10 (IO_L37N_GCLK12_0); also elsewhere on the board
/EPDC_D0P: U700.E10 (IO_L37P_GCLK13_0); also elsewhere on the board
/EPDC_D1N: U700.B10 (IO_L35P_GCLK17_0); also elsewhere on the board
/EPDC_D1P: U700.A10 (IO_L35N_GCLK16_0); also elsewhere on the board
/EPDC_D2N: U700.E11 (IO_L64N_SCP4_0); also elsewhere on the board
/EPDC_D2P: U700.F10 (IO_L64P_SCP5_0); also elsewhere on the board
/EPDC_D3N: U700.D12 (IO_L66N_SCP0_0); also elsewhere on the board
/EPDC_D3P: U700.D11 (IO_L66P_SCP1_0); also elsewhere on the board
/EPDC_D4N: U700.C11 (IO_L39P_0); also elsewhere on the board
/EPDC_D4P: U700.A11 (IO_L39N_0); also elsewhere on the board
/EPDC_D5N: U700.B12 (IO_L62P_0); also elsewhere on the board
/EPDC_D5P: U700.A12 (IO_L62N_VREF_0); also elsewhere on the board
/EPDC_D6N: U700.C13 (IO_L63P_SCP7_0); also elsewhere on the board
/EPDC_D6P: U700.A13 (IO_L63N_SCP6_0); also elsewhere on the board
/EPDC_D7N: U700.B14 (IO_L65P_SCP3_0); also elsewhere on the board
/EPDC_D7P: U700.A14 (IO_L65N_SCP2_0); also elsewhere on the board
/EPDC_GDCLK: U700.B16 (IO_L29N_A22_M1A14_1); also elsewhere on the board
/EPDC_GDOE: U700.D16 (IO_L31N_A18_M1A12_1); also elsewhere on the board
/EPDC_GDSP: U700.C16 (IO_L33N_A14_M1A4_1); also elsewhere on the board
/EPDC_SDCE0: U700.E15 (IO_L34P_A13_M1WE_1); also elsewhere on the board
/EPDC_SDLE: U700.E16 (IO_L34N_A12_M1BA2_1); also elsewhere on the board
/EPDC_SDOE: U700.F15 (IO_L35P_A11_M1A7_1); also elsewhere on the board
/EPDC_SE_CLK: U700.B15 (IO_L29P_A23_M1A13_1); also elsewhere on the board
/EPD_THROT: U700.M16 (IO_L46N_FOE_B_M1DQ3_1); also elsewhere on the board
/FPGA_CLK33: U700.K11 (IO_L42N_GCLK6_TRDY1_M1LDM_1); also elsewhere on the board
/fpga_io/LED: R700.1, U700.C15 (IO_L33P_A15_M1A10_1)
GND: D700.1 (K); also elsewhere on the board
unnamed: D700.2 (A), R700.2

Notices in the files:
pcb/r2-mainboard/epd.kicad_sch:
Copyright 2025 Modos Tech Inc
